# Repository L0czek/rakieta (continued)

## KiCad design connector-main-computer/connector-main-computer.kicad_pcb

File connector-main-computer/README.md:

Connector - main computer
=========================

Purpose

This board aggregates the controller's GPIO and signals into a single 10 m DVI-I cable. It is located near the controller to keep the fragile controller away from the engine and high-risk area.

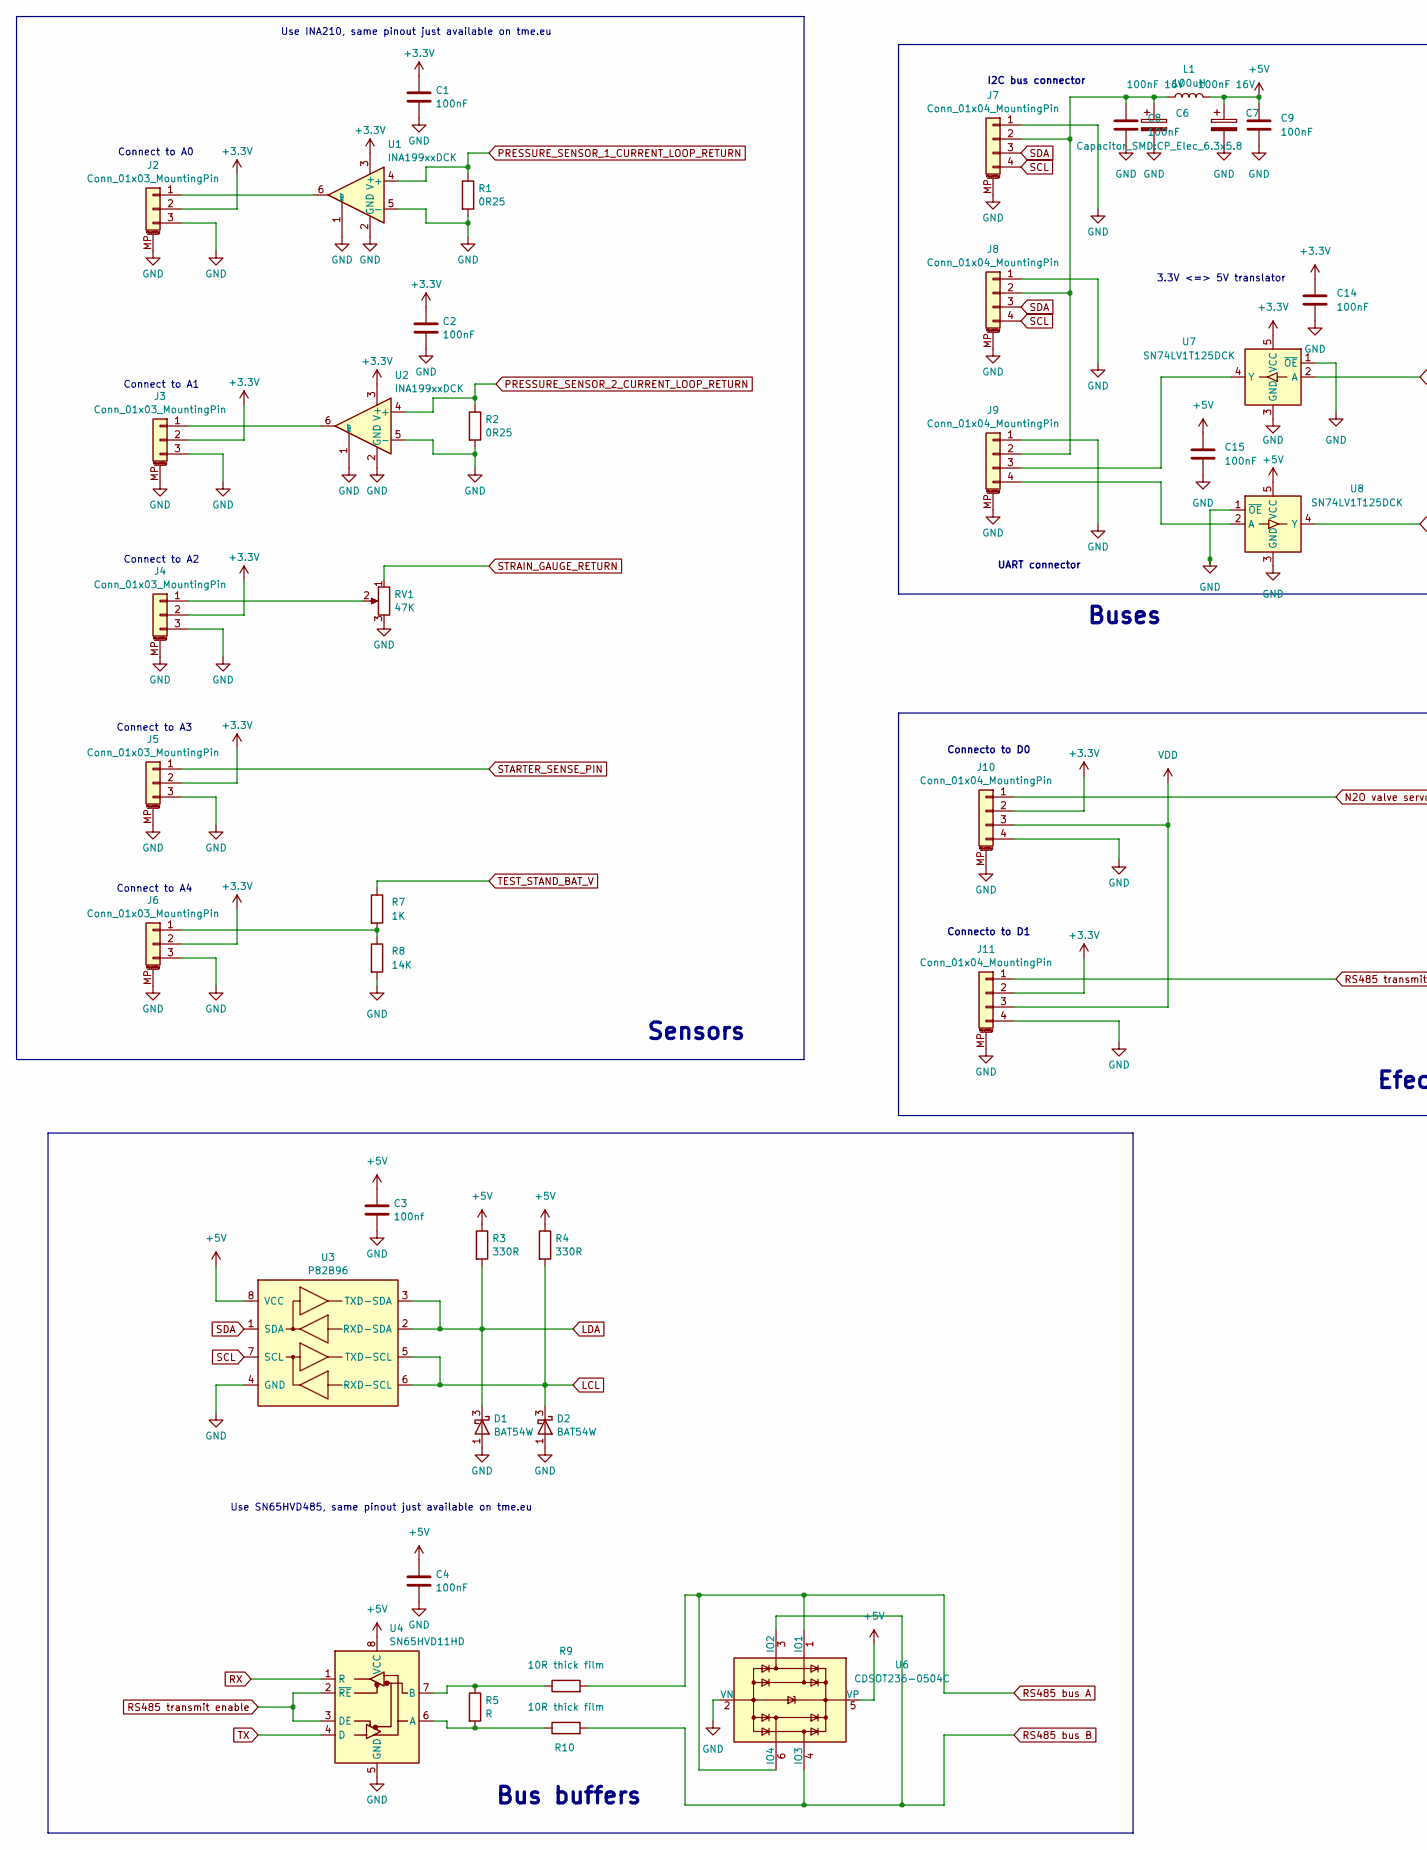
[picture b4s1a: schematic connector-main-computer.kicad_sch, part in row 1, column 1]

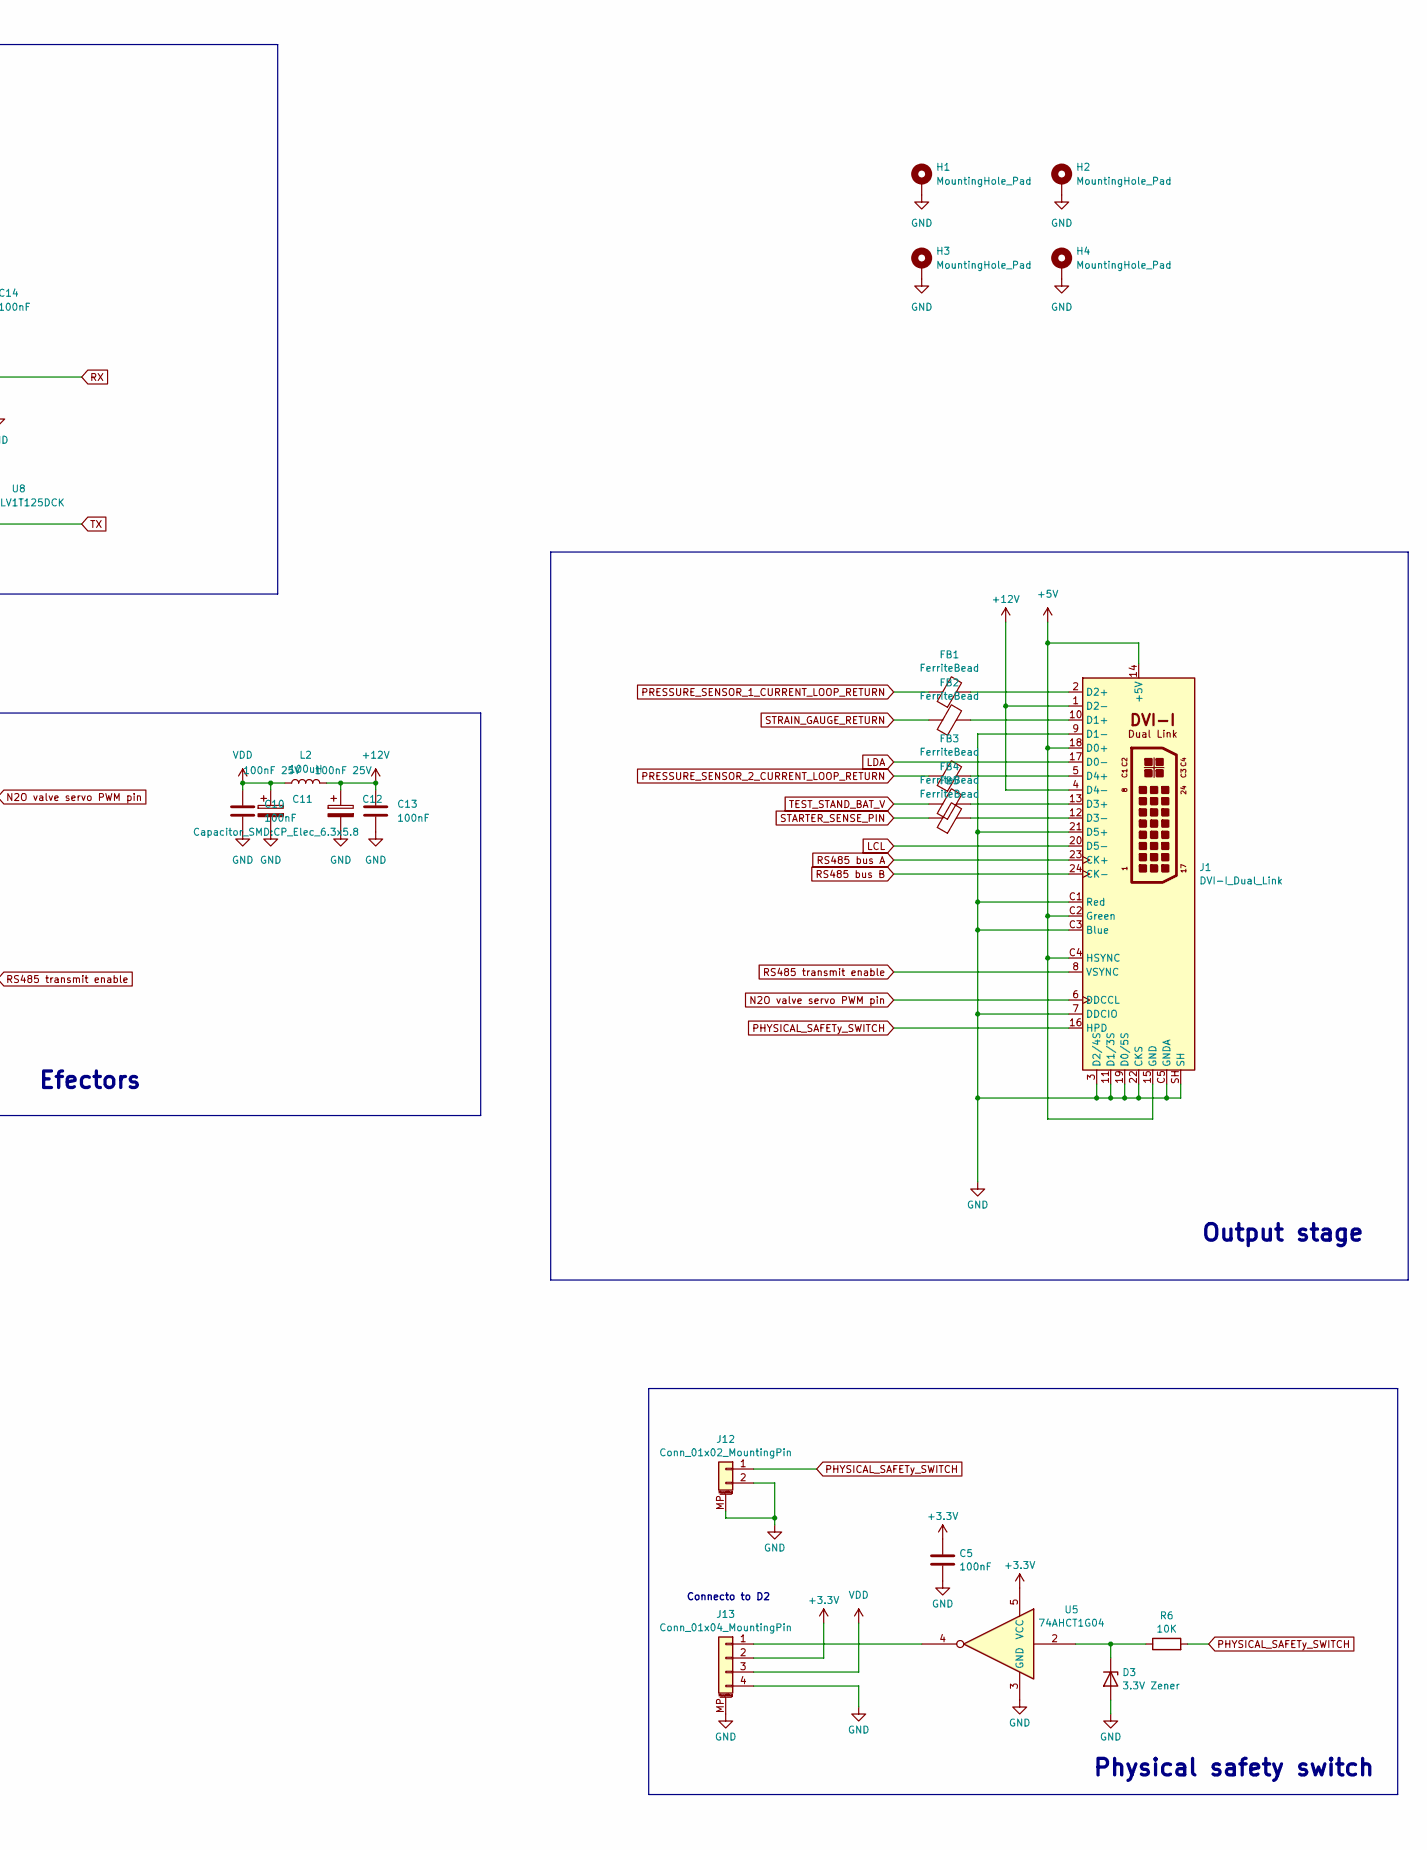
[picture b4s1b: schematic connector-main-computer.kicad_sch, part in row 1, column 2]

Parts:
C1, C2, C4, C5, C8, C9, C10, C13, C14, C15: 100nF; C_0805_2012Metric
C3: 100nf; C_0805_2012Metric
C6, C7: 100nF 16V; CP_Elec_6.3x5.8
C11, C12: 100nF 25V; CP_Elec_6.3x5.8
D1, D2: BAT54W; SOT-323_SC-70
D3: 3.3V Zener; D_MiniMELF
FB1, FB2, FB3, FB4, FB5: FerriteBead; L_0805_2012Metric
H1, H2, H3, H4: MountingHole_Pad; MountingHole_3.2mm_M3_Pad_Via
J1: DVI-I_Dual_Link; DVI-I_Molex_74320-1004_Horizontal
J2, J3, J4, J5, J6: Conn_01x03_MountingPin; JST_PH_S3B-PH-SM4-TB_1x03-1MP_P2.00mm_Horizontal
J7, J8, J9, J10, J11, J13: Conn_01x04_MountingPin; JST_PH_S4B-PH-SM4-TB_1x04-1MP_P2.00mm_Horizontal
J12: Conn_01x02_MountingPin; JST_PH_S2B-PH-SM4-TB_1x02-1MP_P2.00mm_Horizontal
L1, L2: 100uH; L_12x12mm_H8mm
R1, R2: 0R25; R_2512_6332Metric
R3, R4: 330R; R_0805_2012Metric
R5: R; R_2512_6332Metric
R6: 10K; R_0805_2012Metric
R7: 1K; R_0805_2012Metric
R8: 14K; R_0805_2012Metric
R9, R10: 10R thick film; R_0805_2012Metric
RV1: 47K; Potentiometer_Bourns_3266W_Vertical
U1, U2: INA199xxDCK; SOT-363_SC-70-6
U3: P82B96; SO-8_3.9x4.9mm_P1.27mm
U4: SN65HVD11HD; SOIC-8_3.9x4.9mm_P1.27mm
U5: 74AHCT1G04; SOT-23-5
U6: CDSOT236-0504C; SOT-23-6
U7, U8: SN74LV1T125DCK; SOT-353_SC-70-5

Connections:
+3.3V: C1.1, C2.1, C5.1, C14.1, J2.2, J3.2, J4.2, J5.2, J6.2, J10.2, J11.2, J13.2, U1.3 (V+), U2.3 (V+), U5.5 (VCC), U7.5 (VCC)
+5V: C3.1, C4.1, C7.1, C9.1, C15.1, J1.14 (+5V), J1.15 (GND), J1.18 (D0+), J1.C2 (Green), J1.C4 (HSYNC), L1.2, R3.1, R4.1, U3.8 (VCC), U4.8 (VCC), U6.5 (VP), U8.5 (VCC)
+12V: C12.1, C13.1, J1.1 (D2-), J1.4 (D4-), L2.2
GND: C1.2, C2.2, C3.2, C4.2, C5.2, C6.2, C7.2, C8.2, C9.2, C10.2, C11.2, C12.2, C13.2, C14.2, C15.2, D1.1 (A), D2.1 (A), D3.2 (A), H1.1, H2.1, H3.1, H4.1, J1.3 (D2/4S), J1.7 (DDCIO), J1.9 (D1-), J1.11 (D1/3S), J1.19 (D0/5S), J1.21 (D5+), J1.22 (CKS), J1.C1 (Red), J1.C3 (Blue), J1.C5 (GNDA), J1.SH, J2.3, J2.MP (MountPin), J3.3, J3.MP (MountPin), J4.3, J4.MP (MountPin), J5.3, J5.MP (MountPin), J6.3, J6.MP (MountPin), J7.1, J7.MP (MountPin), J8.1, J8.MP (MountPin), J9.1, J9.MP (MountPin), J10.4, J10.MP (MountPin), J11.4, J11.MP (MountPin), J12.2, J12.MP (MountPin), J13.4, J13.MP (MountPin), R1.2, R2.2, R8.2, RV1.3, U1.1 (REF), U1.2 (GND), U1.5 (-), U2.1 (REF), U2.2 (GND), U2.5 (-), U3.4 (GND), U4.5 (GND), U5.3 (GND), U6.2 (VN), U7.1 (~OE), U7.3 (GND), U8.1 (~OE), U8.3 (GND)
LCL: D2.3 (K), J1.20 (D5-), R4.2, U3.5 (TXD-SCL), U3.6 (RXD-SCL)
LDA: D1.3 (K), J1.17 (D0-), R3.2, U3.2 (RXD-SDA), U3.3 (TXD-SDA)
N2O valve servo PWM pin: J1.6 (DDCCL), J10.1
unnamed: D3.1 (K), R6.1, U5.2
unnamed: FB2.2, J1.10 (D1+)
unnamed: FB1.2, J1.2 (D2+)
unnamed: FB4.2, J1.13 (D3+)
unnamed: FB5.2, J1.12 (D3-)
unnamed: FB3.2, J1.5 (D4+)
unnamed: J2.1, U1.6
unnamed: J3.1, U2.6
unnamed: J4.1, RV1.2
unnamed: J6.1, R7.2, R8.1
unnamed: C6.1, C8.1, J7.2, J8.2, J9.2, L1.1
unnamed: J9.3, U7.4 (Y)
unnamed: J9.4, U8.2 (A)
unnamed: J13.1, U5.4
unnamed: R5.2, R10.1, U4.6 (A)
unnamed: R5.1, R9.1, U4.7 (B)
PHYSICAL_SAFETy_SWITCH: J1.16 (HPD), J12.1, R6.2
PRESSURE_SENSOR_1_CURRENT_LOOP_RETURN: FB1.1, R1.1, U1.4 (+)
PRESSURE_SENSOR_2_CURRENT_LOOP_RETURN: FB3.1, R2.1, U2.4 (+)
RS485 bus A: J1.23 (CK+), R9.2, U6.1 (IO1), U6.6 (IO4)
RS485 bus B: J1.24 (CK-), R10.2, U6.3 (IO2), U6.4 (IO3)
RS485 transmit enable: J1.8 (VSYNC), J11.1, U4.2 (~RE), U4.3 (DE)
RX: U4.1 (R), U7.2 (A)
SCL: J7.4, J8.4, U3.7 (SCL)
SDA: J7.3, J8.3, U3.1 (SDA)
STARTER_SENSE_PIN: FB5.1, J5.1
STRAIN_GAUGE_RETURN: FB2.1, RV1.1
TEST_STAND_BAT_V: FB4.1, R7.1
TX: U4.4 (D), U8.4 (Y)
VDD: C10.1, C11.1, J10.3, J11.3, J13.3, L2.1

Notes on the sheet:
Efectors
Connecto to D0
3.3V <=> 5V translator
Connect to A3
Connecto to D1
Connect to A4
Connect to A2
Bus buffers
Physical safety switch
I2C bus connector
Sensors
Output stage
UART connector
Buses
Use INA210, same pinout just available on tme.eu
Connecto to D2
Connect to A1
Connect to A0
Use SN65HVD485, same pinout just available on tme.eu

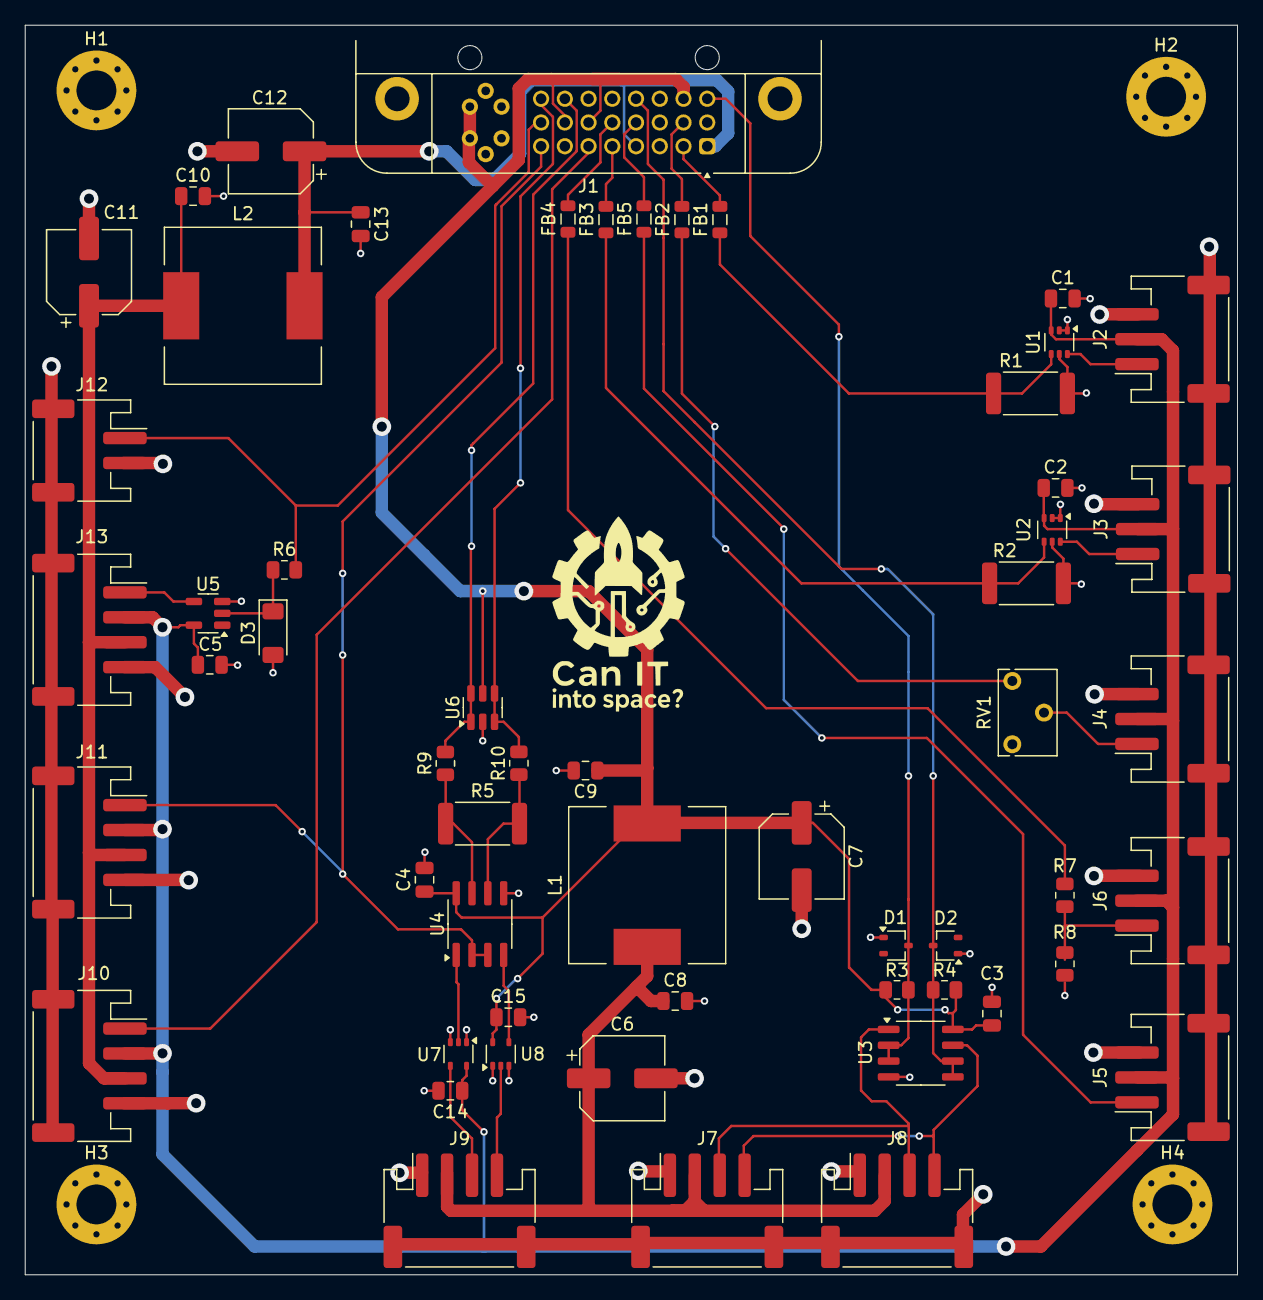
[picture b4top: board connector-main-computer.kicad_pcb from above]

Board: 2 copper layers, 97.3 x 100.3 mm, 61 parts (0 on the bottom side), 37 nets.

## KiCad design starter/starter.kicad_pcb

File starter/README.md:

Starter board
=============

Purpose

The `starter` board provides the ignition impulse to fire the engine. It includes an I2C IO expander and an 8-channel digital comparator to require a correct safety byte/address to be present before firing. The rocket engine is fired by discharging a large battery of capacitors via a high power mosfet.

Features

- Safety: ignition only occurs when the correct I2C address/byte is presented to the IO expander. The sent byte is later compared with fixed value that can be set by encoders on PCB.
- Igniter presence sensing (so an ignition attempt can be inhibited if no igniter detected)

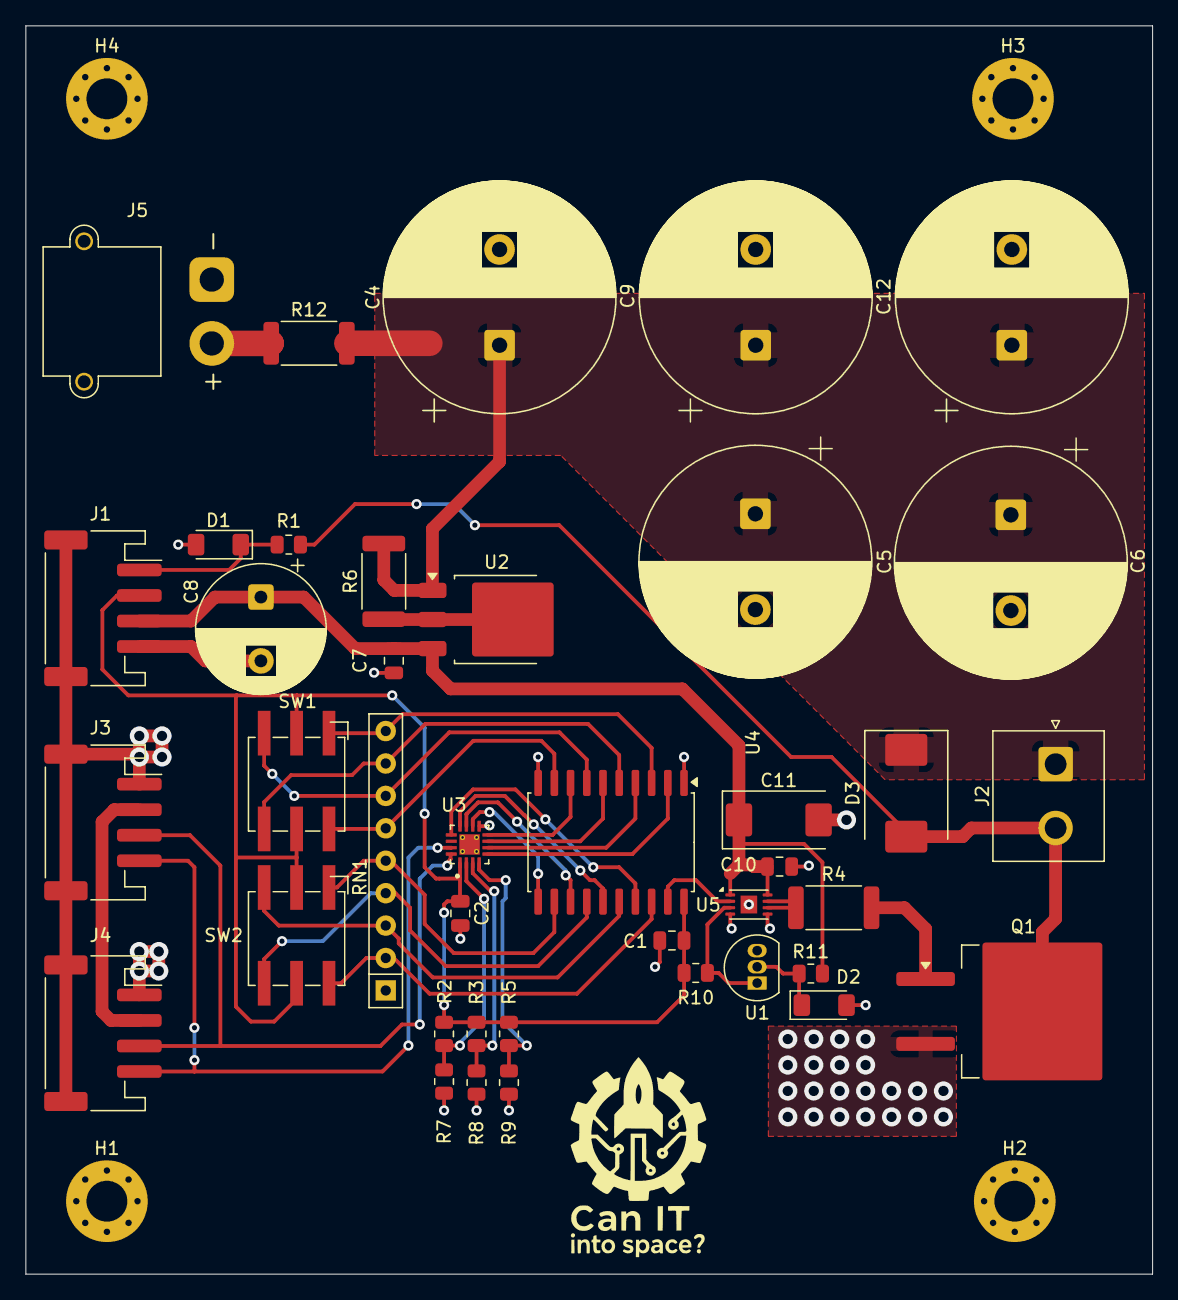
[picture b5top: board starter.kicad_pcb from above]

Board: 2 copper layers, 88.3 x 97.8 mm, 44 parts (0 on the bottom side), 35 nets.

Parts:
C1, C2, C7, C10: C; C_0805_2012Metric
C4, C5, C6, C9, C12: C_Polarized; CP_Radial_D18.0mm_P7.50mm
C8: C_Polarized; CP_Radial_D10.0mm_P5.00mm
C11: C_Polarized; CP_EIA-7343-31_Kemet-D
D1, D2: D_Zener; D_MiniMELF
D3: D; D_SMC
H1, H2, H3, H4: MountingHole; MountingHole_3.2mm_M3_Pad_Via
J1, J3, J4: Conn_01x04_MountingPin; JST_PH_S4B-PH-SM4-TB_1x04-1MP_P2.00mm_Horizontal
J2: Conn_01x02; JST_NV_B02P-NV_1x02_P5.00mm_Vertical
J5: Conn_01x02_MountingPin; AMASS_XT30PW-M_1x02_P2.50mm_Horizontal
Q1: Q_NMOS_GDS; TO-263-2
R1, R2, R3, R5, R7, R8, R9, R10, R11: R; R_0805_2012Metric
R4, R6, R12: R; R_2512_6332Metric
RN1: R_Network08; R_Array_SIP9
SW1, SW2: SW_Coded_SH-7050; Nidec_Copal_SH-7010A
U1: MCP100-475D; TO-92L_Inline
U2: LM1117DT-ADJ; TO-252-3_TabPin2
U3: PCF8574RGTR; QFN50P300X300X100-17N
U4: 74HC688; SOIC-20W_7.5x12.8mm_P1.27mm
U5: MCP14A1201xMNY; TDFN-8-1EP_3x2mm_P0.5mm_EP1.3x1.4mm

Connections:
+3.3V: C1.1, C2.1, J1.2, R2.1, R3.1, R5.1, R10.1, SW1.C, SW2.C, U3.1 (VCC), U4.20 (VCC)
+12V: C7.1, C8.1, C10.1, C11.1, J1.3, R11.1, U2.3 (VI), U5.1 (VDD), U5.8 (VDD)
GND: C1.2, C2.2, C4.2, C5.2, C6.2, C7.2, C8.2, C9.2, C10.2, C11.2, C12.2, D1.2 (A), D2.2 (A), J1.4, J1.MP (MountPin), J3.1, J3.MP (MountPin), J4.1, J4.MP (MountPin), J5.1, Q1.3 (S), R7.2, R8.2, R9.2, RN1.1 (common), U1.3 (VSS), U3.9 (GND), U3.17 (EXP), U4.1 (G), U4.10 (GND), U5.4 (GND), U5.5 (GND), U5.9 (GND)
unnamed: D1.1 (K), J1.1, R1.2
unnamed: D2.1 (K), R11.2, U1.2 (VDD)
unnamed: D3.2 (A), J2.2, Q1.2 (D), R1.1
unnamed: C4.1, C5.1, C6.1, C9.1, C12.1, D3.1 (K), J2.1, R6.2, R12.2, U2.1 (ADJ)
unnamed: J3.2, J4.2
unnamed: J5.2, R12.1
unnamed: Q1.1 (G), R4.2
unnamed: R4.1, U5.6 (~OUT), U5.7 (~OUT)
unnamed: RN1.2 (R1), SW2.8, U4.18 (R7)
unnamed: RN1.3 (R2), SW2.4, U4.16 (R6)
unnamed: RN1.4 (R3), SW2.2, U4.14 (R5)
unnamed: RN1.5 (R4), SW2.1, U4.12 (R4)
unnamed: RN1.6 (R5), SW1.8, U4.9 (R3)
unnamed: RN1.7 (R6), SW1.4, U4.7 (R2)
unnamed: RN1.8 (R7), SW1.2, U4.5 (R1)
unnamed: RN1.9 (R8), SW1.1, U4.3 (R0)
unnamed: R10.2, U1.1 (~RST), U5.3 (EN)
unnamed: R6.1, U2.2 (VO)
unnamed: R2.2, R7.1, U3.2 (A0)
unnamed: R3.2, R8.1, U3.3 (A1)
unnamed: R5.2, R9.1, U3.4 (A2)
unnamed: U3.5 (P0), U4.2 (P0)
unnamed: U3.6 (P1), U4.4 (P1)
unnamed: U3.7 (P2), U4.6 (P2)
unnamed: U3.8 (P3), U4.8 (P3)
unnamed: U3.10 (P4), U4.11 (P4)
unnamed: U3.11 (P5), U4.13 (P5)
unnamed: U3.12 (P6), U4.15 (P6)
unnamed: U3.13 (P7), U4.17 (P7)
unnamed: U4.19 (P=R), U5.2 (IN)
SCL: J3.4, J4.4, U3.15 (SCL)
SDA: J3.3, J4.3, U3.16 (SDA)

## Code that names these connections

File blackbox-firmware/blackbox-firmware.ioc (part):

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Mcu.Name=STM32C011F(4-6)Px
Mcu.Package=TSSOP20
Mcu.UserName=STM32C011F4Px
PA0.Mode=Half_duplex(single_wire_mode)
PA0.Signal=USART1_TX
PA1.GPIOParameters=GPIO_PuPd
PA1.GPIO_PuPd=GPIO_PULLUP
PA1.Signal=GPIO_Input
PA11\ [PA9].Mode=IN11
PA11\ [PA9].Signal=ADC1_IN11
PA13.Mode=Serial_Wire
PA13.Signal=DEBUG_SWDIO
PA14-BOOT0.Mode=Serial_Wire
PA14-BOOT0.Signal=DEBUG_SWCLK
PA2.Signal=GPIO_Output
PA3.Signal=GPIO_Output
PA4.GPIOParameters=GPIO_Speed
PA4.GPIO_Speed=GPIO_SPEED_FREQ_VERY_HIGH
PA4.Signal=GPIO_Output
PA5.Mode=Full_Duplex_Master
PA5.Signal=SPI1_SCK
PA6.Mode=Full_Duplex_Master
PA6.Signal=SPI1_MISO
PA7.Mode=Full_Duplex_Master
PA7.Signal=SPI1_MOSI
PA8.GPIOParameters=GPIO_PuPd
PA8.GPIO_PuPd=GPIO_PULLUP
PA8.Signal=GPIO_Input
PC14-OSCX_IN\ (PC14).Mode=HSE-External-Oscillator-REMAPPED
PC14-OSCX_IN\ (PC14).Signal=RCC_OSCX_IN
PC15-OSCX_OUT\ (PC15).Mode=HSE-External-Oscillator-REMAPPED
PC15-OSCX_OUT\ (PC15).Signal=RCC_OSCX_OUT
RCC.HSE_VALUE=12000000
RCC.SYSCLKFreq_VALUE=48000000
board=custom

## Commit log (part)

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2025-06-29 Add initial idea for starter schematic
2025-06-29 Add schematic in pdf
2025-07-04 Add start pcb
2025-09-08 Update starter to rev 2 with I2C IO expander
2025-09-13 Add high power connector
2025-09-13 Add initial version of main computer connector board
2025-09-13 Add initial version of test stand connector
2025-09-13 Fix power, add buffer
2025-09-23 Add first revision of board for the test stand connector
2025-09-23 Add first revision of board for main computer connector
2025-09-25 add current divider
2025-09-25 change strain power supply
2025-09-27 Logo, fix DRC in starter
2025-09-27 Test stand board improve text, move conector too near border
2025-09-27 Connector main computer texts and move connectors
2025-09-30 Fix uart connection, add crossing and enable negation
2025-09-30 Add values for SMAART wire conevrter and safety rezistor
2025-10-05 Fix footprint for U1 in starter board
2025-10-05 Rework main computer connector
    * Add filtering for 5V and 12V lines
    * Add input protection for RS485
    * Run all test stand logic on 5V - add level translation
2025-10-05 Add value for some elements
2025-10-07 Rework connector test stand board
    * Add values for elements
    * Rework power supply
2025-10-10 Fix footprint for hex encoder
2025-10-14 Add sensor tmp107
2025-10-14 Duuuze pady
2025-10-15 Added capcaitors, text improvements
2025-10-16 Resolve some DRC errors
2025-10-16 Move logo to proper layer
2025-10-16 Update sensor pcb
2025-10-16 Fix rs232 port footprint
2025-10-16 Starter fix
2025-10-16 Connector-main-computer fixes
2025-10-16 Rework connector test stand
2025-10-16 Add labels on port
2025-10-16 Add labels, rework
2025-11-11 Update missing component values
2025-11-18 fixed
2025-11-30 Add blackbox schematic and board design
2025-12-06 blackbox update
2025-12-08 Rework pcb to make it easier to attach mechanically
2025-12-08 Add NOT gate to fix uart, rework silkscreen
2026-01-09 base code
2026-01-10 DMA and simple test
2026-01-13 Add README
2026-01-22 Fixed reads/writes with busy loops, added tests
    There were fun race conditions in DMA
2026-02-21 Import frontend
2026-02-21 Update README graph
2026-02-21 Downsampling
2026-02-21 Perf debugging
2026-02-21 docs: add aviation checklist design and implementation plan
2026-02-21 Less react recalculations
2026-02-21 Fix DB write count and row count by string 1000ms under each key
2026-02-22 feat: add mqtt-synced aviation checklist tab
2026-02-26 Update the sim to run at 1000 Hz
2026-02-26 Refactor to a more performant charts library
2026-02-26 Fix analysis tab after restaring the page
    The slider initial values and thermometer list did not load properly. Also make it start in paused mode when not connected.
2026-02-26 Fix reset button not resetting the connection error state
    Without it, the connection gets stuck in ERROR forever
2026-02-26 chore: ignore local worktree directory
2026-02-26 Switch docker-compose to not run in dev mode
    Dev mode is causing an out-of-memory error after some time
    with the points updating so frequently
2026-02-26 Polish checklist SCADA UI and status cues
2026-02-26 feat: inline current-step checklist controls
2026-02-26 Add configuration tab
2026-02-26 Refine checklist live value and status display
2026-02-26 fix literówka
2026-02-28 Fix packed u12 decoding logic
2026-02-28 Fix default Vref value
2026-02-28 Fix temperature packet format
2026-02-28 Unify labels across the entire frontend
2026-02-28 Fix charts in dashboard tab jumping around
2026-02-28 Clean up RAM history storage
2026-02-28 Update default LUT based on our ESP calibration
2026-02-28 Display servo value in degrees
2026-02-28 Store connection settings in local storage
2026-02-28 Make the event log better
2026-02-28 Fix back in time warnings with retained messages
2026-02-28 Add shutdown button
2026-03-01 Add small charts
2026-03-01 Allow zoom
2026-03-01 Fix tooltip when hovering over less frequent data
2026-03-01 Remove old performance probing code
2026-03-01 Display average fast ADC packet rate
2026-03-03 [WIP] Fix the AI soup
2026-03-08 add frontend skills
2026-03-08 Improve responsive layout and navigation behavior
2026-03-08 Normalize frontend theme and restore chart line colors
2026-03-08 Tokenize frontend theming and color usage
2026-03-08 Trim unnecessary ambient animations
2026-03-08 Add pandas export range controls in analysis
2026-03-08 Fix frontend loading, theming, and analysis panel fit
2026-03-08 Adapt tablet layout and touch targets
2026-03-08 Normalize SCADA tokens and analysis mobile order
2026-03-09 Refine visual effects and interaction emphasis
2026-03-09 Adjust mobile dashboard and analysis layouts
2026-03-09 Add subtle delight interactions and loading polish
2026-03-09 Distill checklist validation and mobile dock
2026-03-09 Refine checklist layout and prevent desktop status wraps
2026-03-09 Fix mobile dashboard scroll and bottom control visibility
2026-03-12 Document firmware behavior and architecture
2026-03-26 chuj wie co, ale działa
2026-03-26 chuj wie co, ale działa, co za chuj zostawił blackbox-wip w tym folderze edition
2026-03-26 Rework status log around DEFMT
2026-03-26 make mosquitto accept 20MB payloads
2026-04-19 Add more capacitors as SD cards are hungry when hotswapped
2026-06-03 Let dashboard status log absorb leftover space on desktop
    Merge the three desktop right-column cells into a single flex column so
    Status Log gets flex-1 instead of a fixed 96px. Power/Thermal/Servo/
    Master Control are intrinsic-sized; Master Control's internal minimums
    tightened to free more space for the log. Thermal sensors capped at
    14.5rem with internal scroll.
2026-06-03 Surface controller health and countdown state
2026-06-29 logo files
